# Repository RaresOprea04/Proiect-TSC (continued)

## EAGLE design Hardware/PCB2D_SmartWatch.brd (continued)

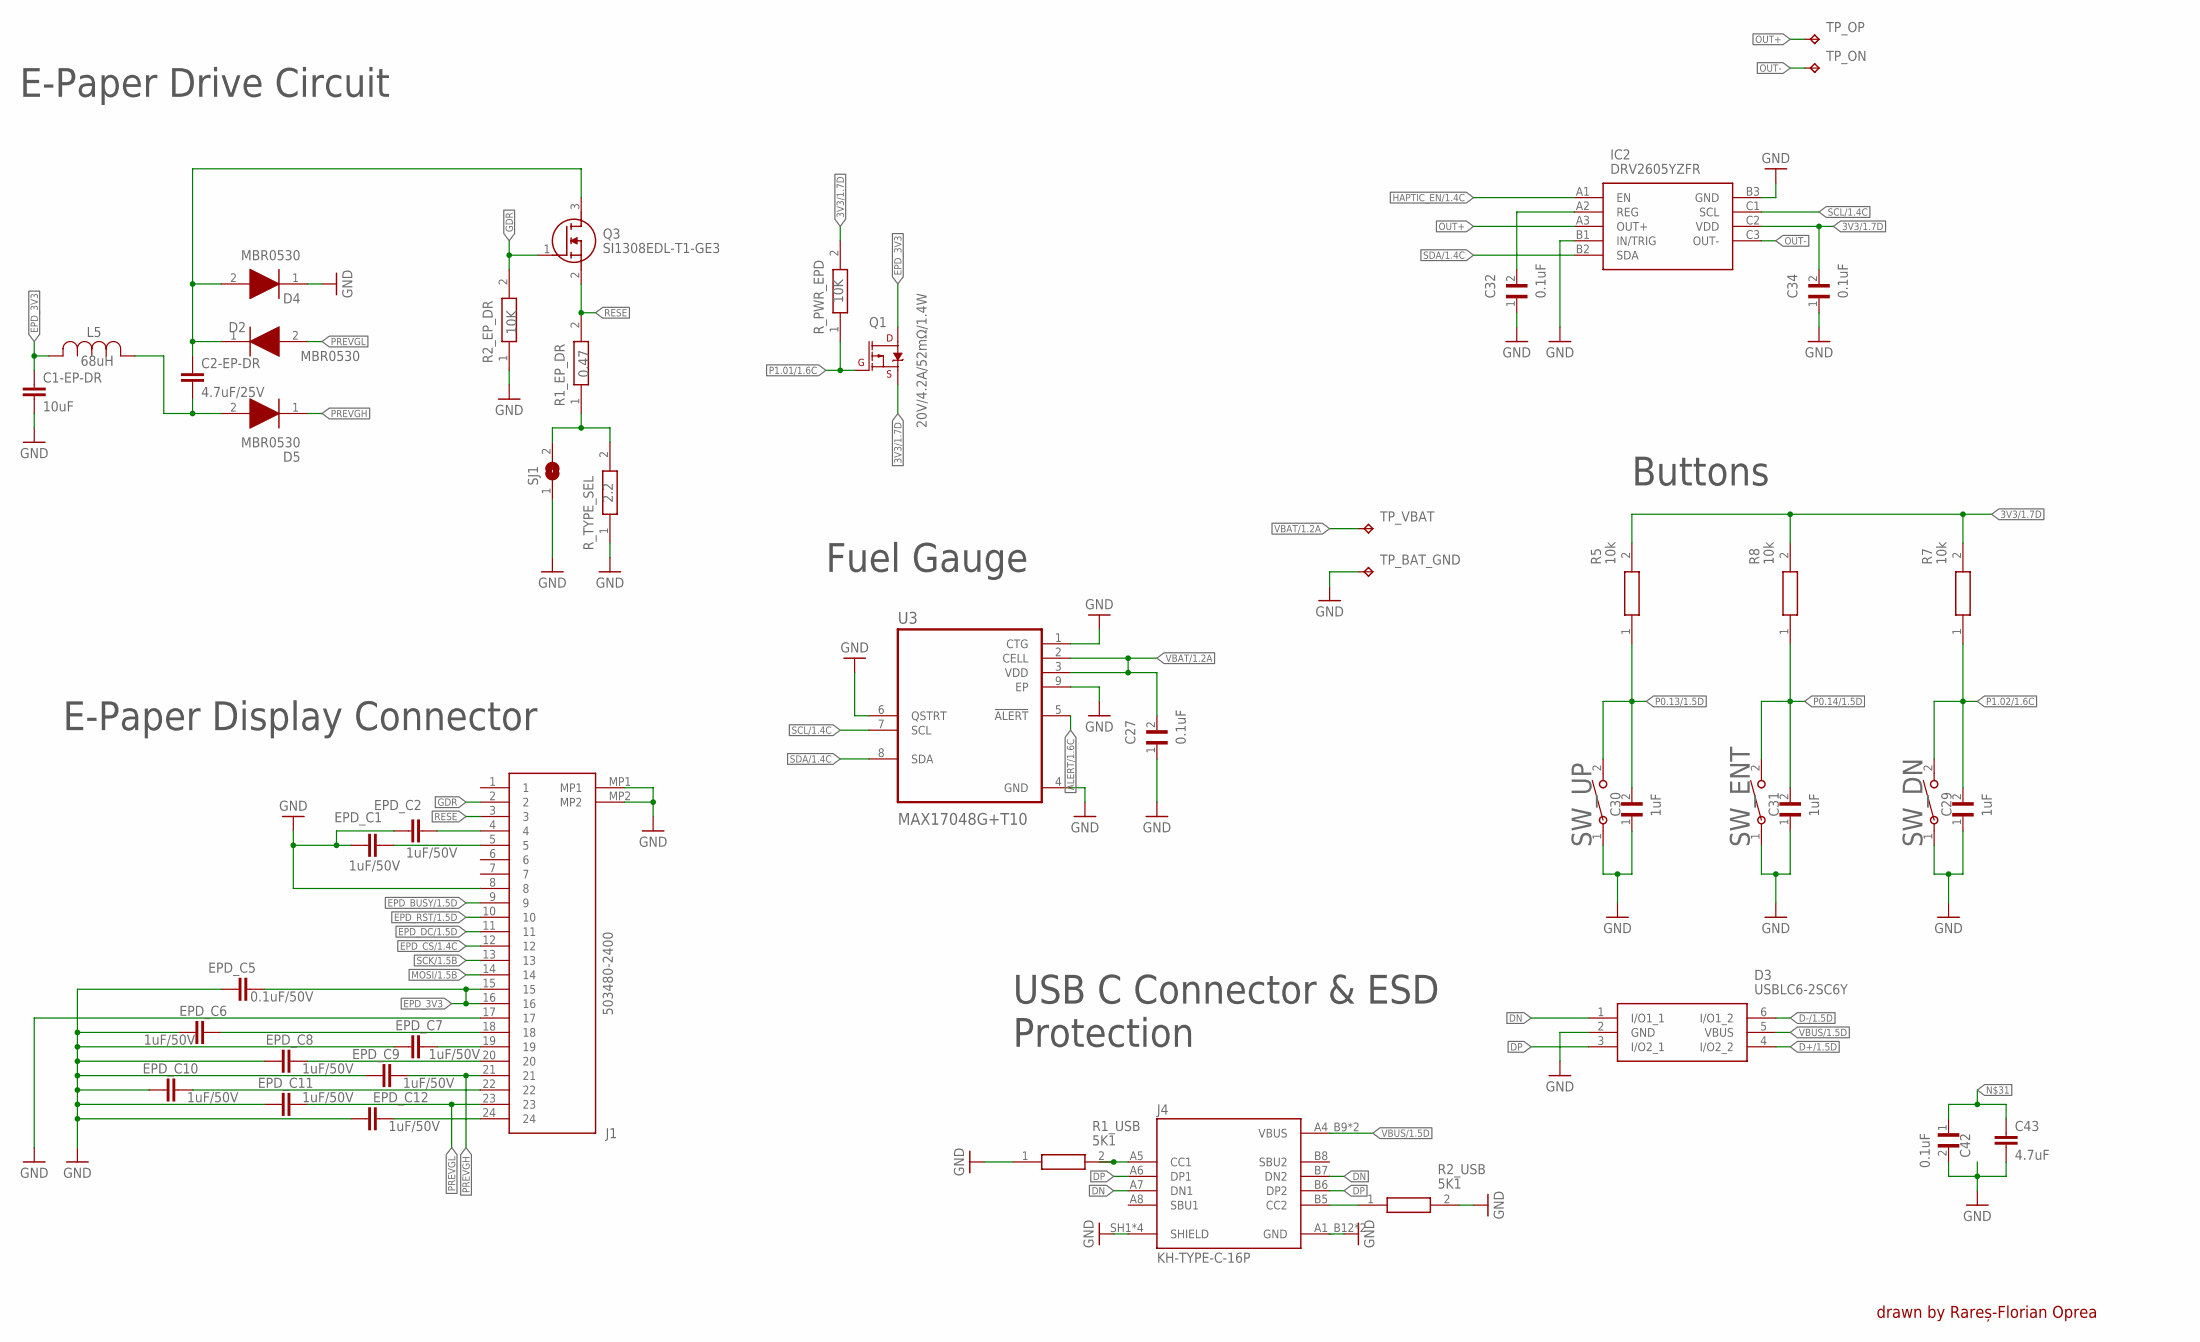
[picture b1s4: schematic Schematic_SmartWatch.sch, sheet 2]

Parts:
C1-EP-DR: 10uF; ESP32_C6_LIBRARY_1_ESP32_WROVER_EAGLE-LTSPICE_C0402
C2-EP-DR: 4.7uF/25V; ESP32_C6_LIBRARY_1_ESP32_WROVER_EAGLE-LTSPICE_C0402
C27, C32, C34: 0.1uF; GRM011R60J152KE01L_2_CAPC0201X13N
C29, C30, C31: 1uF; GRM011R60J152KE01L_2_CAPC0201X13N
C42: 0.1uF; GRM011R60J152KE01L_1_0201
C43: 4.7uF; ESP32_C6_LIBRARY_1_ESP32_WROVER_EAGLE-LTSPICE_C0402
D2, D4, D5: MBR0530; ESP32_C6_LIBRARY_5_SOD3716X135N
D3: USBLC6-2SC6Y; ESP32_C6_LIBRARY_3_SOT95P280X145-6N
EPD_C1, EPD_C2, EPD_C6, EPD_C7, EPD_C8, EPD_C9, EPD_C10, EPD_C11, EPD_C12: 1uF/50V; NORDIC_NRF_3_RESC0201_L
EPD_C5: 0.1uF/50V; NORDIC_NRF_3_RESC0201_L
IC2: DRV2605YZFR; DRV2605YZFR_BGA9C50P3X3_144X144X62
J1: 503480-2400; 503480-2400_5034802400
J4: KH-TYPE-C-16P; KH-TYPE-C-16P_KINGHELM_KH-TYPE-C-16P
L5: 68uH; ESP32_C6_LIBRARY_2_IND_4828-WE-TPC_WRE
Q1: 20V/4.2A/52mΩ/1.4W; ESP32_C6_LIBRARY_4_ESP32_C6_LIBRARY_4_ESP32_C6_LIBRARY_4_ES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
Q3: SI1308EDL-T1-GE3; ESP32_C6_LIBRARY_6_SOT65P210X110-3N
R1_EP_DR: 0.47; ERA-1AEB3401C_0201
R1_USB, R2_USB: 5K1; ERA-1AEB3401C_0201
R2_EP_DR: 10K; ERA-1AEB3401C_0201
R5, R7, R8: 10k; ERA-1AEB3401C_0201
R_PWR_EPD: 10K; ERA-1AEB3401C_0201
R_TYPE_SEL: 2.2; ERA-1AEB3401C_0201
SJ1: ESP32_C6_LIBRARY_7_JUMPER_SJ
SW_DN: 2025-10-22_07-23-44_LIBRARY_EVP-AKE31ASW_EVP-AKE3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; 2025-10-22_07-23-44_LIBRARY_SW_EVP-AKE31A_PAN
SW_ENT: 2025-10-22_07-23-44_LIBRARY_EVP-AKE31ASW_EVP-AKE3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; 2025-10-22_07-23-44_LIBRARY_SW_EVP-AKE31A_PAN
SW_UP: 2025-10-22_07-23-44_LIBRARY_EVP-AKE31ASW_EVP-AKE3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; 2025-10-22_07-23-44_LIBRARY_SW_EVP-AKE31A_PAN
TP_BAT_GND: HECTOR_WATCH_1_TPTP20R; HECTOR_WATCH_1_TP20R
TP_ON: HECTOR_WATCH_1_TPTP20R; HECTOR_WATCH_1_TP20R
TP_OP: HECTOR_WATCH_1_TPTP20R; HECTOR_WATCH_1_TP20R
TP_VBAT: HECTOR_WATCH_1_TPTP20R; HECTOR_WATCH_1_TP20R
U3: MAX17048G+T10; ESP32_C6_LIBRARY_SON50P200X200X80-9N

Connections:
3V3/1.7D: C34.2, IC2.C2 (VDD), Q1.2 (S), R5.2, R7.2, R8.2, R_PWR_EPD.2
ALERT/1.6C: U3.5 (!ALERT)
D+/1.5D: D3.4 (I/O2_2)
D-/1.5D: D3.6 (I/O1_2)
DN: D3.1 (I/O1_1), J4.A7 (DN1), J4.B7 (DN2)
DP: D3.3 (I/O2_1), J4.A6 (DP1), J4.B6 (DP2)
EPD_3V3: C1-EP-DR.1, EPD_C5.2, J1.15, J1.16, L5.2, Q1.3 (D)
EPD_BUSY/1.5D: J1.9
EPD_CS/1.4C: J1.12
EPD_DC/1.5D: J1.11
EPD_RST/1.5D: J1.10
GDR: J1.2, Q3.1 (G), R2_EP_DR.2
GND: C1-EP-DR.2, C27.1, C29.1, C30.1, C31.1, C32.1, C34.1, C42.2, C43.2, D4.1 (K), EPD_C1.1, EPD_C2.1, EPD_C5.1, EPD_C6.1, EPD_C7.1, EPD_C8.1, EPD_C9.1, EPD_C10.1, EPD_C11.1, EPD_C12.1, IC2.B1 (IN/TRIG), J1.8, J1.17, J1.MP1, J1.MP2, J4.A1_B12 (GND), J4.A12_B1 (GND), J4.SH1 (SHIELD), J4.SH2 (SHIELD), J4.SH3 (SHIELD), J4.SH4 (SHIELD), R1_USB.1, R2_EP_DR.1, R2_USB.2, R_TYPE_SEL.1, SJ1.1, SW_DN.1, SW_ENT.1, SW_UP.1, TP_BAT_GND.TP, U3.1 (CTG), U3.4 (GND), U3.6 (QSTRT), U3.9 (EP); also elsewhere on the board
HAPTIC_EN/1.4C: IC2.A1 (EN)
MOSI/1.5B: J1.14
unnamed: EPD_C2.2, J1.4
unnamed: EPD_C1.2, J1.5
unnamed: EPD_C12.2, J1.24
unnamed: R1_EP_DR.1, R_TYPE_SEL.2, SJ1.2
unnamed: C2-EP-DR.2, D5.2 (A), L5.1
unnamed: EPD_C10.2, J1.22
unnamed: C2-EP-DR.1, D2.1 (K), D4.2 (A), Q3.3 (D)
unnamed: EPD_C7.2, J1.19
unnamed: EPD_C8.2, J1.20
unnamed: EPD_C6.2, J1.18
unnamed: C32.2, IC2.A2 (REG)
unnamed: C42.1, C43.1
unnamed: J4.B5 (CC2), R2_USB.1
unnamed: J4.A5 (CC1), R1_USB.2
OUT+: IC2.A3 (OUT+), TP_OP.TP
OUT-: IC2.C3 (OUT-), TP_ON.TP
P0.13/1.5D: C30.2, R5.1, SW_UP.2
P0.14/1.5D: C31.2, R8.1, SW_ENT.2
P1.01/1.6C: Q1.1 (G), R_PWR_EPD.1
P1.02/1.6C: C29.2, R7.1, SW_DN.2
PREVGH: D5.1 (K), EPD_C9.2, J1.21
PREVGL: D2.2 (A), EPD_C11.2, J1.23
RESE: J1.3, Q3.2 (S), R1_EP_DR.2
SCK/1.5B: J1.13
SCL/1.4C: IC2.C1 (SCL), U3.7 (SCL)
SDA/1.4C: IC2.B2 (SDA), U3.8 (SDA)
VBAT/1.2A: C27.2, TP_VBAT.TP, U3.2 (CELL), U3.3 (VDD)
VBUS/1.5D: D3.5 (VBUS), J4.A4_B9 (VBUS), J4.A9_B4 (VBUS)

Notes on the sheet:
drawn by Rareș-Florian Oprea
E-Paper Display Connector
E-Paper Drive Circuit
Fuel Gauge
Buttons
USB C Connector & ESD Protection

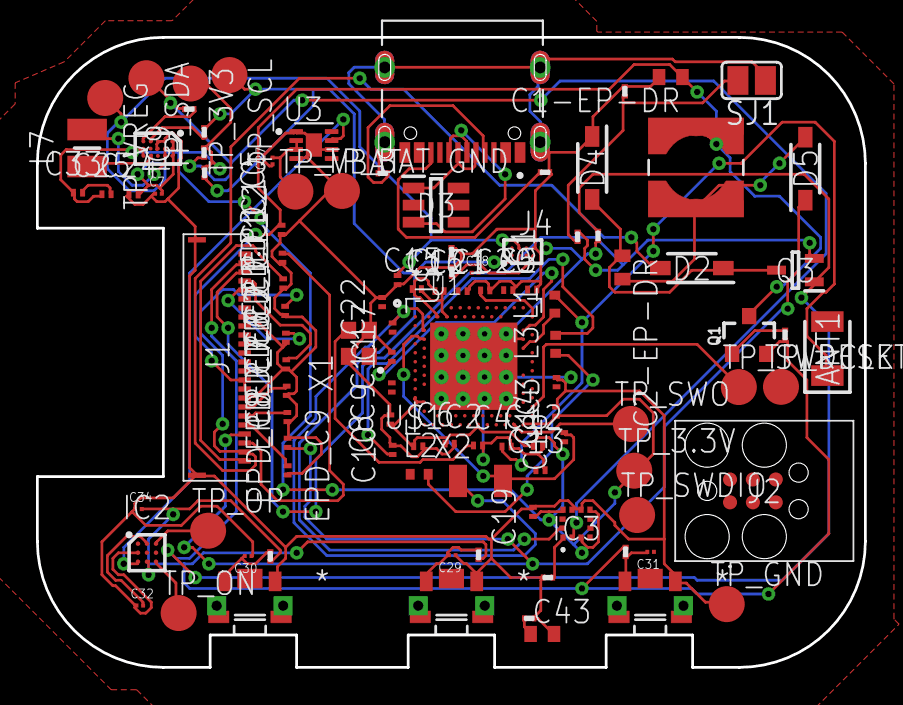
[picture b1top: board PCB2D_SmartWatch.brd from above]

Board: 2 copper layers, 46.0 x 35.0 mm, 105 parts (0 on the bottom side), 70 nets.

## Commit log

2026-04-10 Add project title to README
2026-04-10 Change license from GPL to Apache 2.0
    Replaced the GNU General Public License with the Apache License 2.0.
2026-04-10 Schelet adaugat
2026-04-10 Project Almost Done
2026-04-10 Facut README
2026-04-20 Update pinout information for nRF52840
2026-04-20 Revise README with final project details and images
    Updated project description and images in README.
2026-04-20 Done Project
2026-04-21 Added diagrams
2026-04-21 Try to fix diagrams
